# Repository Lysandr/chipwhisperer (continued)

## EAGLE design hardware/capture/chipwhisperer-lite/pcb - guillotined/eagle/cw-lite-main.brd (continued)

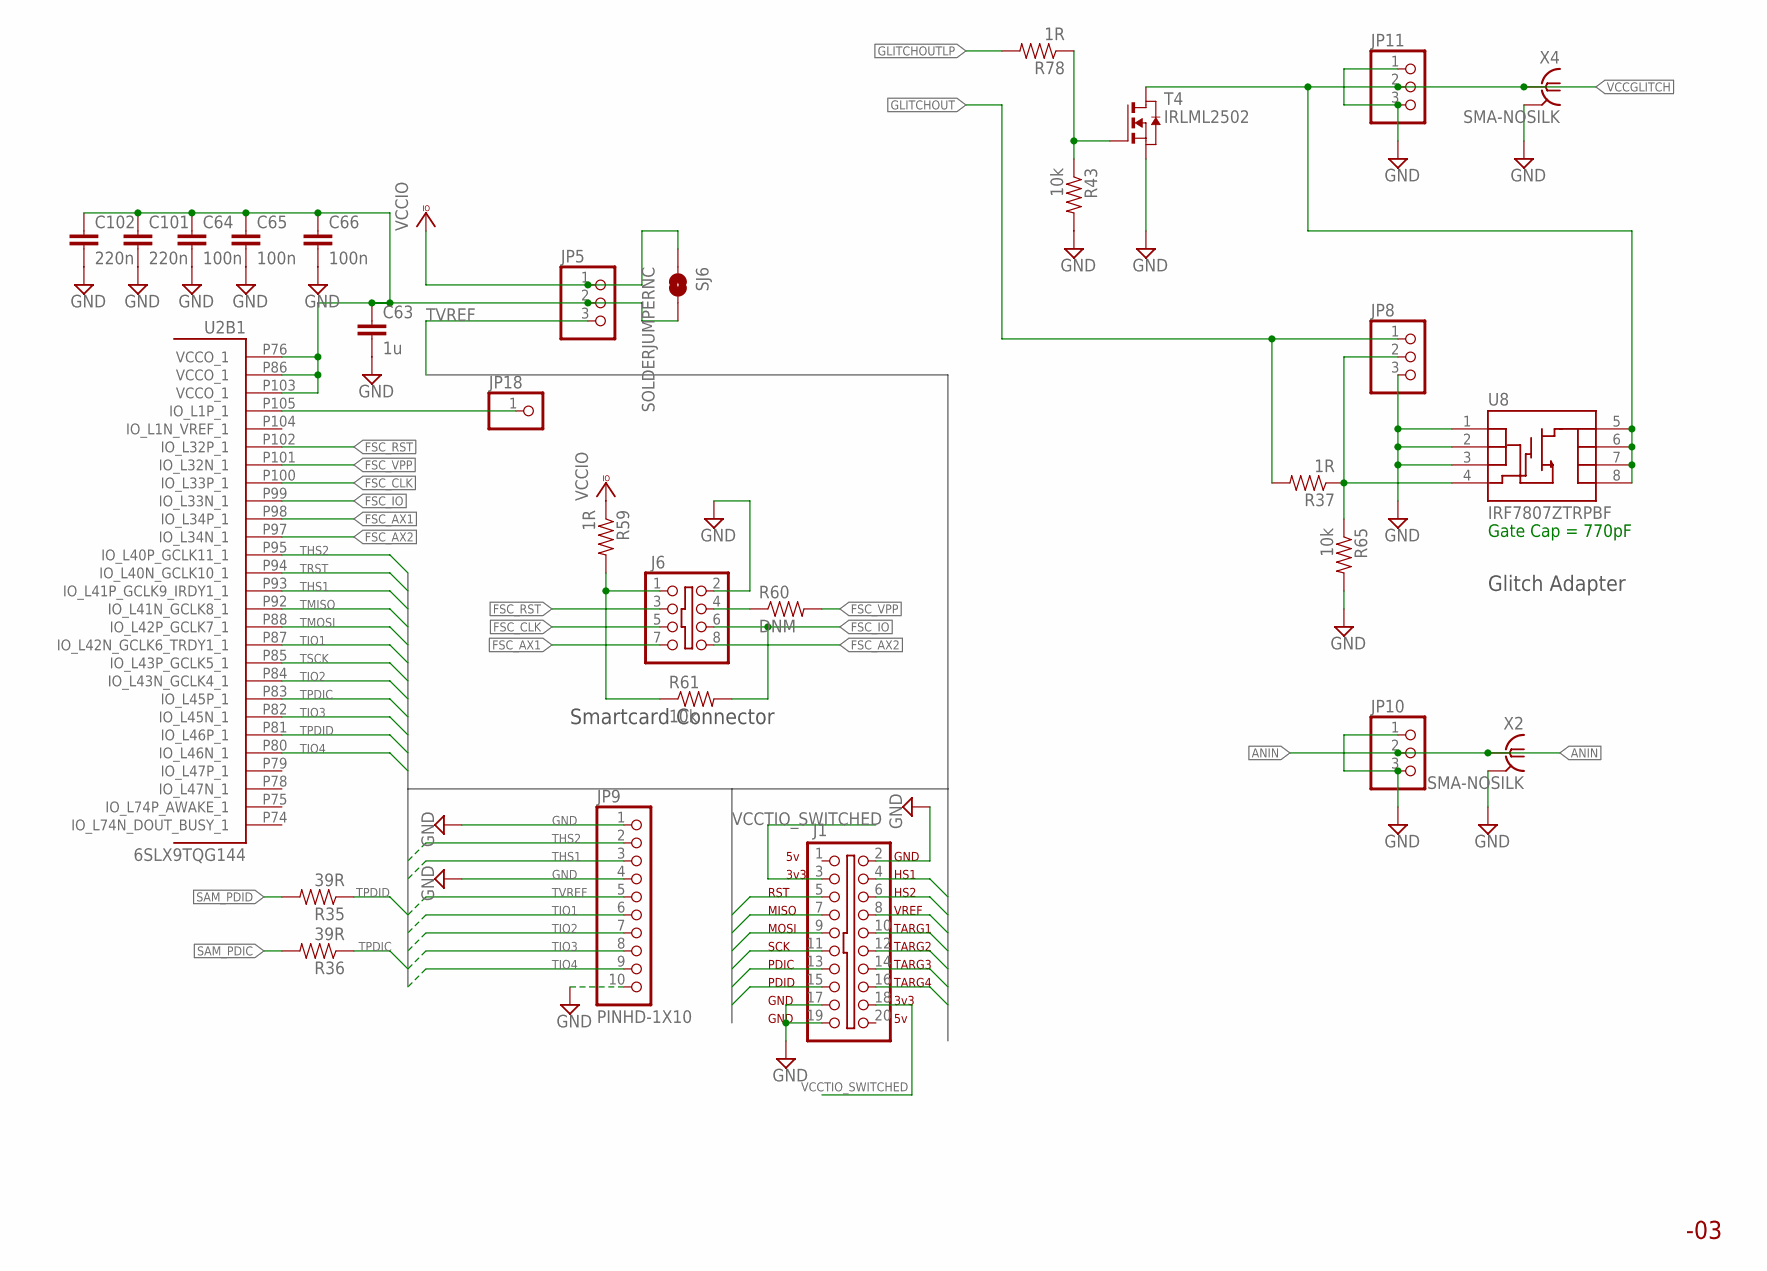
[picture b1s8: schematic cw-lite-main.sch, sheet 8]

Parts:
C63: 1u; 0603C
C64, C65, C66: 100n; 0402C
C101, C102: 220n; 0402C
J1: SHROUD_2X10-SHROUDED; PINSHRD_PTH_2X10
J6: SHROUD_2X4SHROUD; PINSHRD_PTH_2X04
JP5, JP8, JP10, JP11: PINHD-1X3; 1X03
JP9: PINHD-1X10; 1X10-BIG
JP18: PINHD-1X1; 1X01
R35, R36: 39R; 0603R
R37, R59, R78: 1R; 0603R
R43, R61, R65: 10k; 0603R
R60: DNM; 0603R
SJ6: SOLDERJUMPERNC; SJ_2S
T4: IRLML2502; SOT-23; MPN IRLML2502TRPBF
U2: 6SLX9TQG144; TQ144; MPN XC6SLX9-3TQG144C
U8: IRF7807ZTRPBF; SO08
X2, X4: SMA-NOSILK; J502-ND-142-0711-821/826-NOSILK

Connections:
ANIN: JP10.2, X2.1; also elsewhere on the board
FSC_AX1: J6.7, U2.P98 (IO_L34P_1)
FSC_AX2: J6.8, U2.P97 (IO_L34N_1)
FSC_CLK: J6.5, U2.P100 (IO_L33P_1)
FSC_IO: J6.6, R61.2, U2.P99 (IO_L33N_1)
FSC_RST: J6.3, U2.P102 (IO_L32P_1)
FSC_VPP: R60.2, U2.P101 (IO_L32N_1)
GLITCHOUT: JP8.1, R37.2; also elsewhere on the board
GLITCHOUTLP: R78.2; also elsewhere on the board
GND: C63.2, C64.2, C65.2, C66.2, C101.2, C102.2, J1.2, J1.17, J1.19, J6.2, JP8.3, JP9.1, JP9.4, JP9.10, JP10.1, JP10.3, JP11.1, JP11.3, R43.2, R65.2, T4.2 (S), U8.1 (S), U8.2 (S), U8.3 (S), X2.G@1 (2), X2.G@2 (2), X2.G@3 (2), X2.G@4 (2), X4.G@1 (2), X4.G@2 (2), X4.G@3 (2), X4.G@4 (2); also elsewhere on the board
unnamed: JP8.2, R37.1, R65.1, U8.4 (G)
unnamed: JP18.1, U2.P105 (IO_L1P_1)
unnamed: R43.1, R78.1, T4.3 (G)
unnamed: J6.1, R59.2, R61.1
unnamed: J6.4, R60.1
SAM_PDIC: R36.2; also elsewhere on the board
SAM_PDID: R35.2; also elsewhere on the board
TARGET_VCCIO: C63.1, C64.1, C65.1, C66.1, C101.1, C102.1, JP5.2, SJ6.2, U2.P76 (VCCO_1), U2.P86 (VCCO_1), U2.P103 (VCCO_1)
THS1: J1.4, JP9.3, U2.P93 (IO_L41P_GCLK9_IRDY1_1)
THS2: J1.6, JP9.2, U2.P95 (IO_L40P_GCLK11_1)
TIO1: J1.10, JP9.6, U2.P87 (IO_L42N_GCLK6_TRDY1_1)
TIO2: J1.12, JP9.7, U2.P84 (IO_L43N_GCLK4_1)
TIO3: J1.14, JP9.8, U2.P82 (IO_L45N_1)
TIO4: J1.16, JP9.9, U2.P80 (IO_L46N_1)
TMISO: J1.7, U2.P92 (IO_L41N_GCLK8_1)
TMOSI: J1.9, U2.P88 (IO_L42P_GCLK7_1)
TPDIC: J1.13, R36.1, U2.P83 (IO_L45P_1)
TPDID: J1.15, R35.1, U2.P81 (IO_L46P_1)
TRST: J1.5, U2.P94 (IO_L40N_GCLK10_1)
TSCK: J1.11, U2.P85 (IO_L43P_GCLK5_1)
TVREF: J1.8, JP5.3, JP9.5
VCCGLITCH: JP11.2, T4.1 (D), U8.5 (D), U8.6 (D), U8.7 (D), U8.8 (D), X4.1
VCCIO: JP5.1, R59.1, SJ6.1; also elsewhere on the board
VCCTIO_SWITCHED: J1.3, J1.18; also elsewhere on the board

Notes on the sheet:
HS1
HS2
VREF
TARG1
TARG2
TARG3
TARG4
3v3
RST
MISO
MOSI
SCK
PDIC
PDID
GND
Glitch Adapter
Smartcard Connector
Gate Cap = 770pF

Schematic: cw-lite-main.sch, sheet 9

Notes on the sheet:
Breakaway Section of PCB

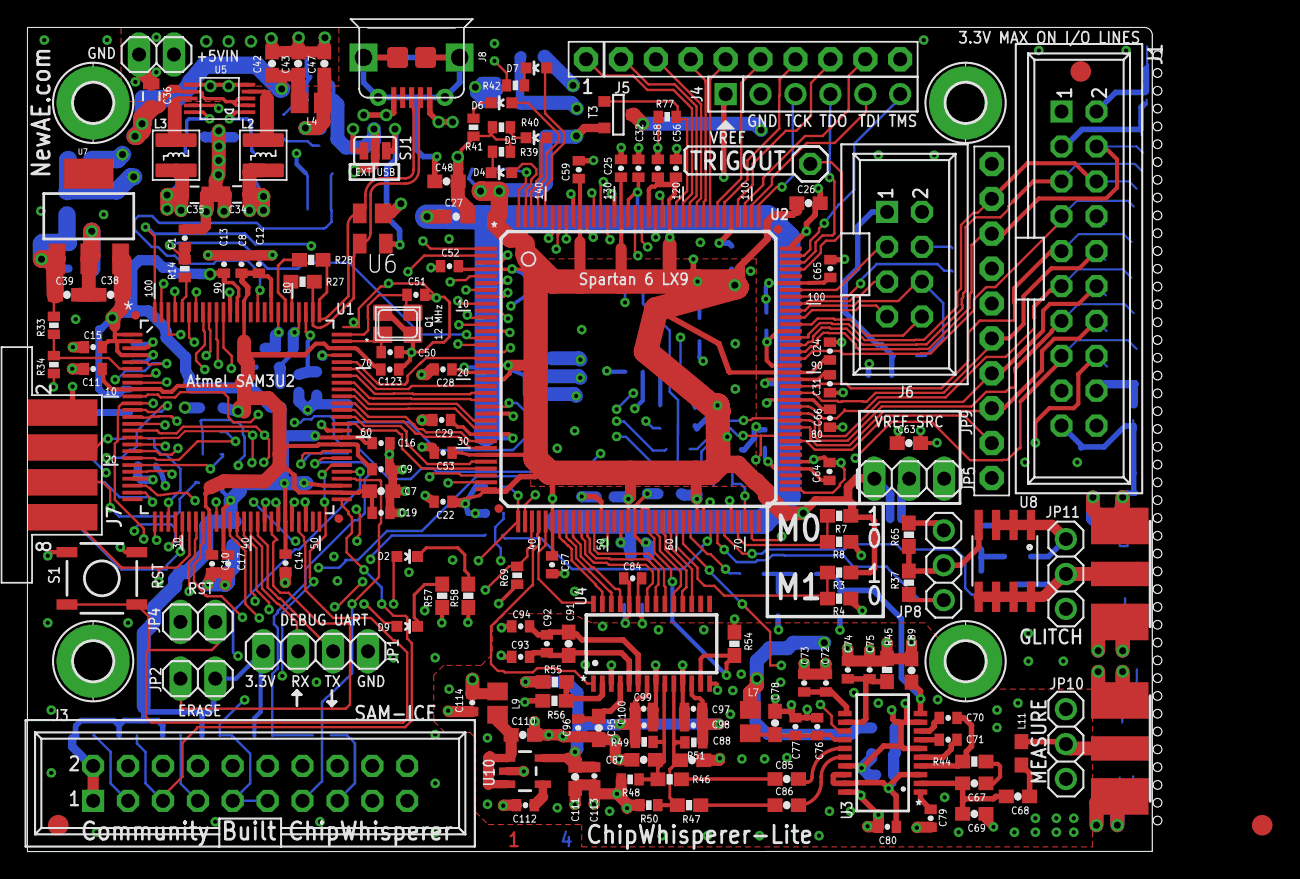
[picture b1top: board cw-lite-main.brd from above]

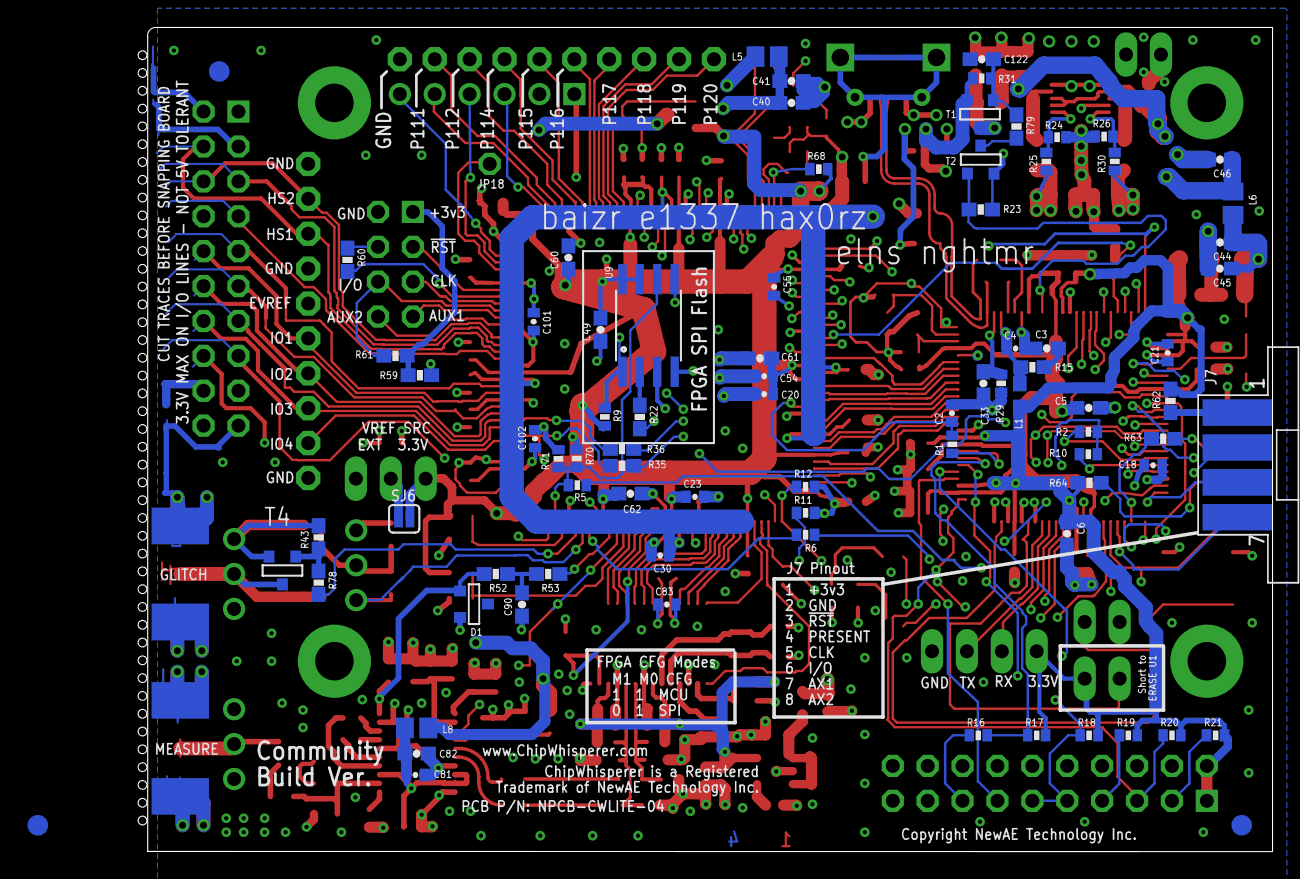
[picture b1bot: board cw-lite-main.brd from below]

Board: 4 copper layers, 81.9 x 60.0 mm, 245 parts (81 on the bottom side), 198 nets.

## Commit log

2020-10-10 beheading right-side of board, getting rid of components, generating new design files

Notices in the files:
hardware/capture/chipwhisperer-lite/pcb - guillotined/eagle/cw-lite-main.brd:
Copyright NewAE Technology Inc.
parts and their libraries:
SparkFun: Licensing: CC v3.0 Share-Alike You are welcome to use this library for commercial purposes.
SparkFun-PowerIC: Licensing: Creative Commons ShareAlike 4.0 International - https://creativecommons.org/licenses/by-sa/4.0
